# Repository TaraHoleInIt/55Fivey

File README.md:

# 55Fivey
An extremely simple astable 555 timer board.

# Pictures
Front

Back

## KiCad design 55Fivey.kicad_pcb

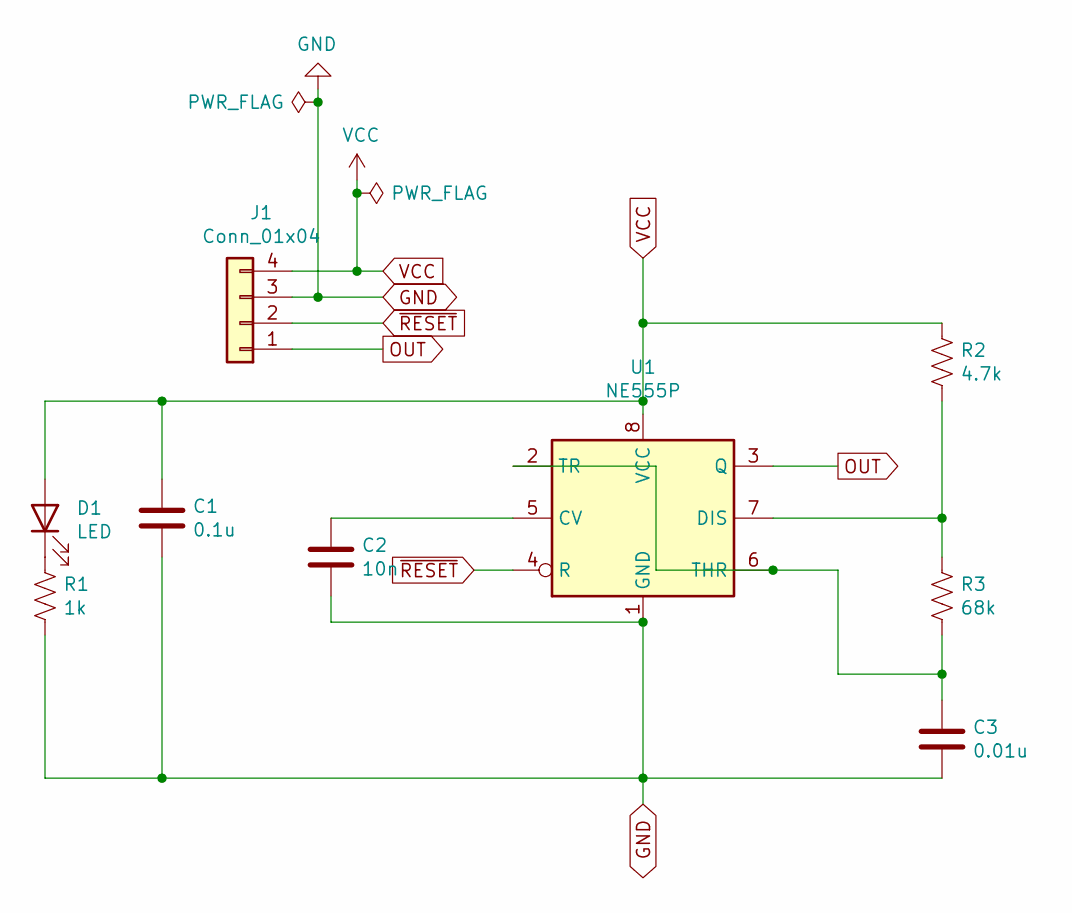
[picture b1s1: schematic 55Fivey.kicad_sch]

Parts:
C1: 0.1u; C_0805_2012Metric_Pad1.18x1.45mm_HandSolder
C2: 10n; C_0805_2012Metric_Pad1.18x1.45mm_HandSolder
C3: 0.01u; C_0805_2012Metric_Pad1.18x1.45mm_HandSolder
D1: LED; LED_0805_2012Metric_Pad1.15x1.40mm_HandSolder
J1: Conn_01x04; PinHeader_1x04_P2.54mm_Horizontal
R1: 1k; R_0805_2012Metric_Pad1.20x1.40mm_HandSolder
R2: 4.7k; R_0805_2012Metric_Pad1.20x1.40mm_HandSolder
R3: 68k; R_0805_2012Metric_Pad1.20x1.40mm_HandSolder
U1: NE555P; SOIC-8_3.9x4.9mm_P1.27mm

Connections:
GND: C1.2, C2.2, C3.2, J1.3, R1.2, U1.1 (GND)
unnamed: C2.1, U1.5 (CV)
unnamed: C3.1, R3.2, U1.2 (TR), U1.6 (THR)
unnamed: D1.1 (K), R1.1
unnamed: R2.2, R3.1, U1.7 (DIS)
OUT: J1.1, U1.3 (Q)
VCC: C1.1, D1.2 (A), J1.4, R2.1, U1.8 (VCC)
~RESET: J1.2, U1.4 (R)

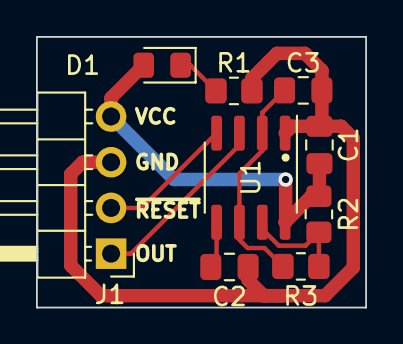
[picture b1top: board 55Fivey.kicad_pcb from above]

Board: 2 copper layers, 18.3 x 15.0 mm, 9 parts (0 on the bottom side), 8 nets.

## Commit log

2021-10-03 Initial
